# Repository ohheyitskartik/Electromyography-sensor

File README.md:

# Electromyography-sensor
The following sensor design can amplify, filter &amp; rectify EMG potentials range between less than 50 μV and up to 30 mV  to a 0-3V logic level compatible with arduino's and arm processors inbuilt adc logic level. Open Readme file for more info.

The above mentioned circuit contains :-
1) Differential Op-amp (G=110).
2) Active high pass-filter set at 106.6 Hz.
3) Active low pass-filter set at 1.97 KHz.
4) Active rectification to avoid any damage to your microcontroller from negative voltages.
5) A variable gain at end to control output voltage.

The git contains :- 
- Schematic of the circuit (.Eagle file).
- PCB Design (.Eagle file).
- Parts list with packages and names (.TXT file).
- Images for the breadboard version of the device, PCB design, cad render and output screenshots.

The putput of the device was taken using NI mydaq device - 
Without any muscle movement (placement on forearm).

With muscle movement (placement on forearm).

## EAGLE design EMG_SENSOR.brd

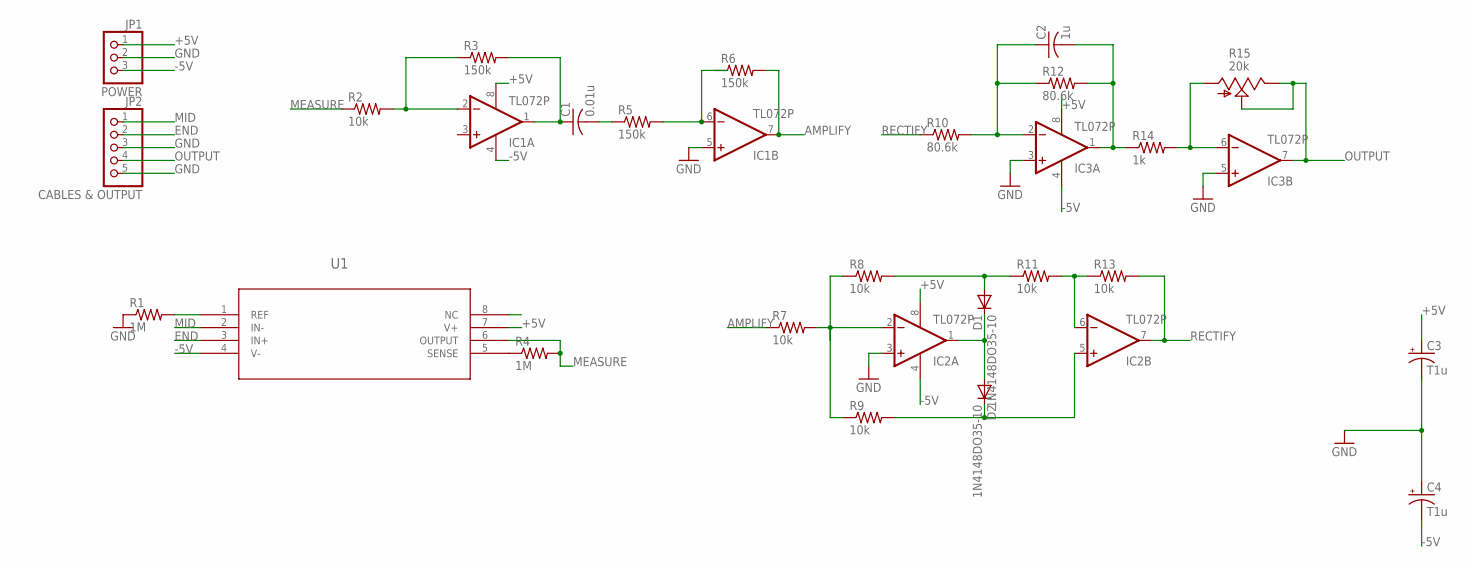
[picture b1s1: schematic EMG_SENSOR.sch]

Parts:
C1: 0.01u; C1206K
C2: 1u; C1206K; MPN MC0805Y104M500A2.54MM
C3, C4: T1u; E2-4
D1, D2: 1N4148DO35-10; DO35-10
IC1, IC2, IC3: TL072P; DIL08
JP1: POWER; 1X03
JP2: CABLES & OUTPUT; 1X05
R1, R4: 1M; R1206W
R2, R7, R8, R9, R11, R13: 10k; R1206W
R3, R5, R6: 150k; R1206W
R10, R12: 80.6k; R1206W
R14: 1k; R1206W
R15: 20k; B25P
U1: INA106_P_8; P8

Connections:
+5V: C3.+, IC1.8 (V+), IC2.8 (V+), IC3.8 (V+), JP1.1, U1.7 (V+)
-5V: C4.-, IC1.4 (V-), IC2.4 (V-), IC3.4 (V-), JP1.3, U1.4 (V-)
AMPLIFY: IC1.7 (OUT), R6.2, R7.1
END: JP2.2, U1.3 (IN+)
GND: C3.-, C4.+, IC1.5 (+IN), IC2.3 (+IN), IC3.3 (+IN), IC3.5 (+IN), JP1.2, JP2.3, JP2.5, R1.1
MEASURE: R2.1, R4.2, U1.6 (OUTPUT)
MID: JP2.1, U1.2 (IN-)
unnamed: IC2.2 (-IN), R7.2, R9.1
unnamed: IC2.6 (-IN), R11.2, R13.1
unnamed: IC1.2 (-IN), R2.2, R3.1
unnamed: C1.1, IC1.1 (OUT), R3.2
unnamed: C1.2, R5.1
unnamed: R4.1, U1.5 (SENSE)
unnamed: IC1.6 (-IN), R5.2
unnamed: D1.C, D2.A, IC2.1 (OUT)
unnamed: D1.A, R8.2, R11.1
unnamed: C2.1, IC3.2 (-IN), R10.2, R12.1
unnamed: D2.C, IC2.5 (+IN), R9.2
unnamed: C2.2, IC3.1 (OUT), R12.2, R14.1
unnamed: IC3.6 (-IN), R14.2, R15.A
OUTPUT: IC3.7 (OUT), JP2.4, R15.E, R15.S
RECTIFY: IC2.7 (OUT), R10.1, R13.2

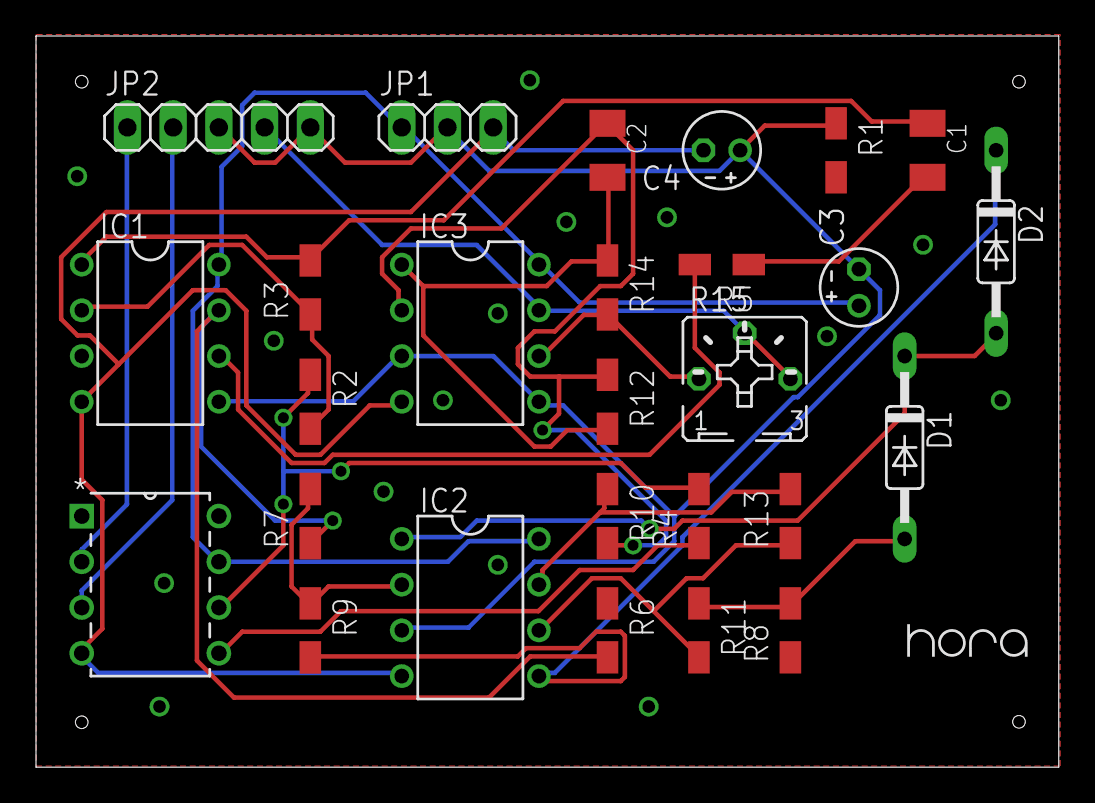
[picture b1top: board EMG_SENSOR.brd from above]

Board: 2 copper layers, 56.8 x 40.6 mm, 27 parts (0 on the bottom side), 22 nets.

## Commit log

2019-03-31 Final-task
    Final EMG Board design
2019-03-31 Revert "Update EMG_SENSOR.brd"
    This reverts commit 2c1e3195e62d11b7e3e16a25b7b5c478b3a32b3b.
2019-03-31 Revert "Final-task"
    This reverts commit 8a2adc822e130e4cf756d79e198dd36a2c16bd06.
2019-03-31 Final commit
2019-03-31 Final commit images
2019-04-02 README.md
    Read this for complete explanation of files.
2019-04-02 Set theme jekyll-theme-cayman
2019-04-02 Set theme jekyll-theme-minimal
